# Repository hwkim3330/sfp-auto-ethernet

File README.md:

# sfp-auto-ethernet

SFP 모듈 세 가지. 호스트와는 SerDes로 붙고, 바깥쪽은 차량 이더넷이나 RJ45로 나간다.

- **폼팩터와 핀:** SFP(INF-8074i, SFF-8419)를 따른다. 전원·제어 핀과 EEPROM(SFF-8472)도 같다.
- **호스트 쪽 조건:**
  - T1과 T1S는 SGMII 1.25 Gbaud라서, 호스트 포트가 SGMII를 해야 한다. 1000BASE-X 전용 포트나 광모듈만 가정한 NIC에서는 안 된다.
  - RJ45는 2500BASE-X 3.125 Gbaud라서 "2.5G SFP"다. 1G 전용 SFP 슬롯에서는 안 되고, 2500BASE-X를 지원하는 포트(대개 SFP+ 케이지)가 필요하다.
- **표준이 아닌 부분:** 차량 이더넷(BASE-T1, T1S)을 SFP에 넣는 표준은 없다. SFF-8024에도 100/1000BASE-T1, 10BASE-T1S 코드가 없다. 그래서 EEPROM은 호스트에 1000BASE-T(RJ45는 2.5GBASE-T) 계열로 보이게 하고, 실제 매체는 벤더 영역에 적는다. 이것은 호환을 위한 우회이고, "표준 차량용 SFP"가 아니다. Intrepid나 Technica의 BASE-T1 SFP도 각사 자체 방식이다.
- **첫 검증 범위:** 정확히 아는 호스트 하나(D10 또는 LAN9692 EVB)로 한정한다. 범용 호환은 1차 목표가 아니다.

> **SFP 엣지 (2026-10-06 발견, 2026-10-08 세 보드 모두 수정):** 엣지 커넥터가 좌우 반전으로 그려져 있었다(SFF-8419 그림 7-2와 반대). 반전이 남아 있으면 VccT가 GND와 닿는다. T1, RJ45, T1S 모두 다시 배치·배선했고, 핑거 20개의 위치와 넷을 생성기와 독립된 기준으로 다시 확인했다([docs/COMPLIANCE.md](docs/COMPLIANCE.md) 3절).

| 변형 | 바깥쪽 | PHY | 호스트 쪽 | 커넥터 | 상태 |
|---|---|---|---|---|---|
| [`t1`](hw/t1/) | **100/1000BASE-T1** | TI DP83TG720S (1000) / DP83TC812S (100): 핀 호환이라 PCB 하나로 둘 다 | SGMII 1.25 Gbaud | H-MTD (Rosenberger E6S20A) | **엣지 수정 후 재배선(2026-10-07): DRC 0 / 미연결 0, ERC 0, KiCad 9 PASS, 주문 파일 있음.** MDI 종단은 TI OA 구성(1 kΩ 0.75 W 2010). 시제품 2~3장 후보. 실물·실측은 아직 없음 |
| [`rj45`](hw/rj45/) | 100M / 1G / **2.5GBASE-T** | Realtek RTL8221B-VB | 2500BASE-X 3.125 Gbaud 또는 SGMII | RJ45 (Kinghelm KH-RJ45-58, 차폐) | **엣지 수정 후 재배선(2026-10-07):** PHY를 윗면으로 옮겼다. DRC 0 / 미연결 0, ERC 0, KiCad 9 PASS, 패널 오류 0. SerDes와 MDI 모두 비아 없이 곧게 간다. 실물·실측은 아직 없음 |
| [`t1s`](hw/t1s/) | 10BASE-T1S | FPGA (Gowin GW5AT-15, SGMII PCS 브리지) + Microchip LAN8670 | SGMII 10 Mb/s | 2핀 (JST PH) | **엣지 수정 후 재배선(2026-10-08): DRC 0 / 미연결 0, ERC 0, KiCad 9 PASS, 패널 오류 0.** 두 SGMII 레인 모두 극성 그대로(게이트웨어 반전 없음). **주문 금지:** Gowin 트랜시버 IP 생성, 합성, P&R, 타이밍, 비트스트림이 끝나기 전에는 PCB를 주문하지 않는다 |

## 구조

```
 host SFP cage ── SerDes (AC 결합, 모듈 안) ──┐
                                              ▼
 I²C 0x50/0x51/0x56 ── STM32G031 ── MDIO ──► PHY ── (자기소자 / CMC) ── 커넥터
 TX_DISABLE · RX_LOS ──┘                      ▲
 3.3 V ── 페라이트 ── 부하 스위치(소프트 스타트) ── 벅 1.0 / 0.95 V ─┘
```

- **MCU 하나가 세 가지 일을 한다.** 호스트에게는 EEPROM(A0h/A2h)과 PHY 브리지(I²C 0x56)로 보이고, 링크 제어도 맡는다. 리눅스 `sfp` 드라이버가 기대하는 방식을 그대로 따랐다([docs/LINUX.md](docs/LINUX.md)).
- **데이터시트가 공개된 부품만 쓴다.** NDA가 필요한 PHY로는 설계도 유지보수도 못 한다. 88Q2112를 고르지 않은 이유다([docs/PARTS.md](docs/PARTS.md)). 예외는 하나, RJ45의 RTL8221B다: 누구나 내려받을 수 있지만 "CONFIDENTIAL" 도장이 찍힌 데이터시트이고, 2.5G를 하는 공개 데이터시트 PHY가 없어서 골랐다(같은 문서에 이유).
- **T1S에는 SGMII PHY가 없다.** 그래서 작은 FPGA가 SGMII 10 Mb/s를 받아 MII로 바꾸고, 반이중 버퍼도 맡는다.

## 설계 원칙 (설계 검토 뒤)

- **적층** (모두 1.0 mm, 같은 3313 프리프레그라 쌍 치수가 같다):
  - **T1은 4층 F / GND / GND / B** (JLC04101H-3313). 두 안쪽 층 모두 GND다. In2에는 저속 신호도 지나가지만, 아래층(B)을 달리는 고속 쌍 밑에는 금지 구역을 두어 판을 온전히 남긴다.
  - **RJ45·T1S는 6층 F / GND / 신호 / +3V3 / GND / B** (JLC06101H-3313). T1S는 In4 GND 안에 0.95 V 코어 섬을 둔다.
  - 그래서 모든 고속 쌍이 어느 층에 있든 GND를 기준으로 삼는다.
- **고속 쌍은 손으로 결합해서 깐다.** 선폭 0.114, 간격 0.152로 약 100 Ω 차동이다.
  - 쌍 안의 두 선은 같은 층, 같은 비아 수로 간다.
  - 층을 바꾸는 곳 옆에는 GND 비아를 둔다.
  - 라우터(Freerouting)는 나머지 저속 신호만 맡는다.
- **3.3 V 인러시**: 핫플러그하면 호스트 필터가 전압을 수십 µs 만에 올린다. 그래서 모듈 입력에 **TPS22918 부하 스위치**(약 3.6 ms 상승)를 넣었다. MSA의 "정상 상태 대비 +30 mA 이내"를 설계로 맞췄다. **실물 측정은 아직이다.**
- **보드 몸통은 폭 11.8 mm**다. 탭은 9.2 mm, 케이지 안 높이 한도는 위 4.65 mm, 아래 1.65 mm다. 치수 출처는 [docs/SFP_MSA.md](docs/SFP_MSA.md)에 있다.

## 검증 (하드웨어 없이 할 수 있는 것)

| 무엇 | 도구 | 어디서 |
|---|---|---|
| DRC, 회로도-PCB 일치(parity), ERC | KiCad 9 (공식 Docker 이미지). 검토자가 여는 그대로 | `sh hw/check_kicad9.sh t1`, `… rj45`, `… t1s` |
| 펌웨어 빌드: 4가지 변형, 경고 0 | arm-none-eabi-gcc | `fw/`, CI |
| T1S 게이트웨어 | Icarus Verilog 테스트벤치 3개 | `hw/t1s/gw/`, CI |
| 규격 대조: 임피던스(자체 2D 전계 해석기), 쌍 스큐 대 심볼 시간, 엣지 핑거 치수, 케이지 높이, 클럭 ppm, 제어 핀 타이밍, 커넥터 | `tools/zsolve.py`, `tools/compliance.py` | [docs/COMPLIANCE.md](docs/COMPLIANCE.md) |
| 레퍼런스 대조: TI·Realtek·Microchip·Gowin 데이터시트·앱노트·EVM, 리눅스 드라이버, 상용 모듈 | 문서별 값 대조 | [docs/REFERENCES.md](docs/REFERENCES.md) |

- GitHub Actions([.github/workflows/check.yml](.github/workflows/check.yml))가 push할 때마다 위 셋을 다시 돌린다.
- KiCad 9 검사에서 허용하는 경고는 "라이브러리 사본이 다르다" 두 종류뿐이다. KiCad 9 라이브러리가 KiCad 7 원본보다 새 판이라서 생긴다.

## 아직 실물로만 확인할 수 있는 것

- **펌웨어는 보드에서 0회 돌았다.** 보드가 오면 확인할 것:
  - MDC/MDIO 타이밍, 시작 시퀀스, TX_DISABLE/RX_LOS 동작;
  - SGMII 극성(세 보드 모두 반전 없이 P–P로 깔았다).
- **인러시 전류와 3.3 V 상승 시간.** 오실로스코프로 잰다.
- **H-MTD 풋프린트.** `hw/t1/fab/t1-1to1.pdf`를 100 %로 인쇄하고 실물 커넥터를 대 본다.
- **골드 핑거.** JLC는 경질 금(hard gold)을 하지 않고 ENIG만 한다. MSA 규격(경질 금 ≥ 0.38 µm)은 아니다. 시험용 삽입 수십 회는 쓸 만하다. 반복 삽입이 많다면 경질 금을 하는 업체(예: PCBWay)에 맡긴다.
- **RJ45 코 폭 17 mm.** 잭 자체가 15.7 mm다. D10에서 옆 포트와 부딪히는지 실측해야 한다.

## Kontron D10에 꽂는다면

[docs/D10.md](docs/D10.md): D10의 SFP 포트는 **최대 2.5G**다.
- T1: `make HOST=d10` 펌웨어로 굽는다(1000BASE-X로 보이고 SGMII AN은 끈다).
- RJ45: 호스트 쪽을 2500BASE-X로 고정한다. D10이 2.5G-T 모듈을 속도 2500 고정에서만 붙이기 때문이다.

## 다음

1. T1S 게이트웨어: Gowin 트랜시버 IP 생성, 합성, 타이밍
2. 하우징: 래치와 베일

## 참고

- 비슷한 상용 제품이 있다. 그러니 이 크기 안에 들어간다.
  - [Intrepid 88Q2112 SFP](https://intrepidcs.com/products/automotive-ethernet-tools/88q2112-1000base-t1-sfp/): 76.5 × 13.5 × 20.5 mm, H-MTD
  - [Technica TE-1441](https://technica-engineering.de/en-gb/hardware-products/sfp-sfp-modules): I²C → MDIO 게이트웨이, DIP 스위치
- 10G RJ45 SFP+는 만들지 않는다. 10GBASE-T PHY는 2.5–5 W를 쓰고 NDA 부품이다. 게다가 D10 포트는 2.5G까지다.

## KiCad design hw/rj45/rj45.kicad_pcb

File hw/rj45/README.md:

# RJ45 SFP: 100M / 1G / 2.5GBASE-T

A copper SFP built around the Realtek RTL8221B. It runs 2500BASE-X (3.125 Gbaud) or SGMII to the host, and 100M / 1G / 2.5GBASE-T on the jack.

Schematic, 6-layer PCB (routed), fab outputs and a JLC panel are all in place.
**Order files are in [`jlc/`](jlc/), and the order sheet is [ORDER.md](ORDER.md).** Nothing has been built.

| Top | Bottom |
|---|---|
|  |  |

## Status

| | Result | How it was checked |
|---|---|---|
| Schematic | **ERC 0 errors, 0 warnings** ([erc.rpt](erc.rpt)) | eeschema's own ERC (`run_erc.sh`) |
| Placement | 70 footprints, no overlaps; housing height limits met | `make_rj45.py` |
| Routing | **DRC 0 violations, 0 unconnected** ([drc.rpt](drc.rpt)) | hand-laid pairs and buses, Freerouting 1.9.0 for the rest, then KiCad DRC |
| KiCad 9 | **DRC 0 errors, 0 unconnected, schematic parity clean, ERC 0 errors** ([kicad9-drc.rpt](kicad9-drc.rpt), [kicad9-erc.rpt](kicad9-erc.rpt)) | `sh ../check_kicad9.sh rj45`: the official KiCad 9 image. Only warnings are "differs from the library copy" |
| Fab | Gerbers + drill ([fab/rj45-gerbers.zip](fab/rj45-gerbers.zip)), [BOM](fab/rj45-bom.csv), [CPL](fab/rj45-cpl.csv), [1:1 print](fab/rj45-1to1.pdf) | `export_rj45.py` |
| Panel | 5 boards, 71.5 × 107.1 mm, **DRC 0 errors, 0 unconnected** with the board's rules ([jlc/panel-drc.rpt](jlc/panel-drc.rpt)) | `panel_rj45.py` (KiKit) |
| Pair lengths | [lengths.txt](lengths.txt) | `make_rj45.py` |

## Parts (all in JLC stock, 2026-09-30)

| | Part | LCSC | Stock |
|---|---|---|---|
| PHY | Realtek RTL8221B-VB-CG | C5155988 | 4564 |
| Magnetics | LINK-PP LP72450ANL (2.5G, 4 channels, 15.2 × 7.1 × 4.3 mm) | C53281905 | 800 |
| Jack | Kinghelm KH-RJ45-58-8P8C, shielded, no magnetics | C2683360 | 2717 |
| Clock | MST8011AI 25 MHz oscillator (≤ 2 ps RMS jitter, as the PHY asks) | C51026225 | 898 |
| Core 0.946 V | TPS62822 buck, 57.6k / 100k | C473385 | 2288 |
| Inrush | TPS22918 load switch, 2.2 nF CT (≈ 3.6 ms) | C131941 | 12874 |
| MCU | STM32G031F6P6 | C529333 | 1454 |

Parts come to about $11 a board.

## Board

- The body is 11.8 mm wide up to the cage front. From there a 17 mm nose carries the jack, which sits entirely outside the cage. The board is 64.4 mm long.
- **Six layers, JLC06101H-3313.** The same 3313 prepreg (0.0994 mm, Dk 4.1) sits under F and B as on the 4-layer stack, so the pairs keep 0.114 mm lines with a 0.152 mm gap (≈ 100 Ω differential).

  | Layer | Use |
  |---|---|
  | F | U1 and its decaps, both SerDes pairs, the MDI pairs under the magnetics, the line side |
  | In1 | GND |
  | In2 | the slow lines, hand-laid end to end (fingers and U1 to the MCU) |
  | In3 | +3V3 plane |
  | In4 | GND |
  | B | the buck, the power-entry caps, the oscillator and analog beads, line pair 2, the MCU |

- **Why six:** on four layers every signal routed, but the PHY's power pins did not all reach their rails. They sit 0.4 mm apart with their decaps right next to them. Here every +3V3 pad has its own via into the In3 plane.
- **Pairs, all laid by hand and coupled** (`make_rj45.py`):
  - SerDes to the host. U1 sits on top, turned 90°. Its pins 37–41 read HSON, HSOP, HSIP, HSIN top to bottom, the order of the SFP edge's RD−, RD+, TD+, TD− (SFF-8419 Figure 7-2). Both pairs run straight, P to P, on top, with no via.
    (Until 2026-10 the edge was drawn mirrored and U1 sat underneath for the same reason; `make_rj45.py` turns that group over.)
  - The four MDI pairs run on top under the magnetics' body and straight into its chip-side pads, in port order: port 0 on channel 1 (jack 1/2) … port 3 on channel 4. CFG_OPT1 is pulled down, so there is no MDI swap.
- **PHY address straps:** the RTL8221B has no internal pulls on its CONFIG pins (datasheet 7.18: an external pull-high or pull-low is required). LED0/1/2 carry PHYAD[2:0]: R19-R21, 4.7 kΩ to ground, give 000, which the PHY treats as address 1 (Table 16 note 2), the address the firmware uses. Three 0201s right above pins 33-35 on top; C16 moved underneath its via and C17 0.3 mm west to make room.
  - Line pairs 0, 1 and 3 run on top in lanes 0.8 mm apart.
  - Line pair 2 (jack pins 4/5) drops to the bottom under its pads. Pair 3/6 straddles 4/5 on the jack, so one of those two pairs has to leave the top side.
- **The MCU sits under the jack.** It is the only place with room. Its ten slow lines run on In2, laid by hand from end to end:
  - they leave the fingers and U1 through vias;
  - they run in the board's lane order to the jack's pin field;
  - they cross the field in three lanes of three, plus MDIO underneath.
  - The MCU's GPIOs are assigned to match the lane order, not the T1 board's: PA0 MDIO, PA1 MDC, PA4 TX_FAULT, PA5 TX_DISABLE, PA6 RX_LOS (`fw/main.c`, `VARIANT_RJ45`).
- **In2 keepouts:** the MDI and line pairs are 2.5GBASE-T at 200 MBd PAM16, so In2 lines may cross under them. On six layers the bottom pairs reference In4 GND anyway.

## Regenerating

```bash
python3 make_rj45.py            # symbols, footprints, schematic, placed PCB
python3 make_rj45.py --route    # planes, dogbones, Freerouting, pours, repairs, DRC -> drc.rpt
sh run_erc.sh                   # eeschema ERC -> erc.rpt
sh ../check_kicad9.sh rj45      # the same board in KiCad 9
python3 export_rj45.py          # gerbers (6 copper layers), BOM, CPL, previews, 1:1 PDF -> fab/
python3 panel_rj45.py           # 5-board panel + JLC files -> jlc/
```

## Not verified

- Nothing has been built.
- **Firmware for this variant** (`fw/`, `VARIANT=rj45`) builds, but has never run. Check:
  - the MDIO access to the RTL8221B;
  - 2500BASE-X / SGMII selection;
  - LED / link reporting.
- **Jack land:** it is drawn from Kinghelm's drawing by hand. Print `fab/rj45-1to1.pdf` at 100 % and set a real jack on it.
- **Fit next to other modules:** the jack is 15.7 mm wide, against 13.7 mm for a copper SFP's housing. It may touch its neighbour in a ganged cage (for example on the D10). Measure it.
- **Inrush and the 0.95 V rise time:** measure them.

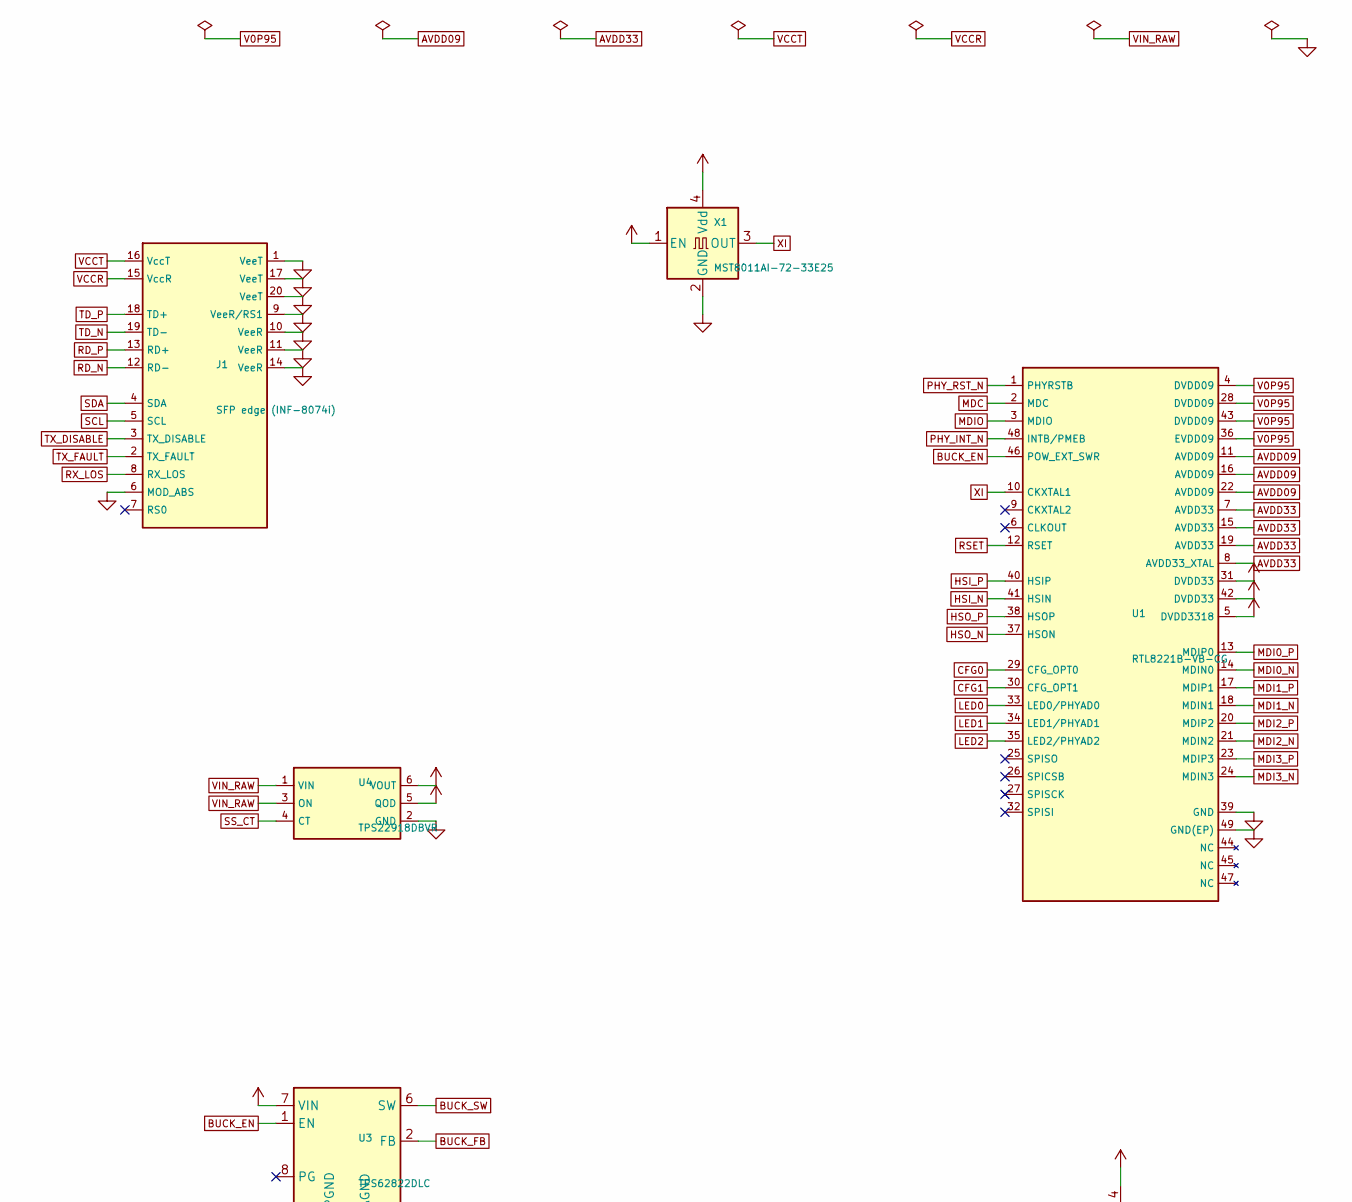
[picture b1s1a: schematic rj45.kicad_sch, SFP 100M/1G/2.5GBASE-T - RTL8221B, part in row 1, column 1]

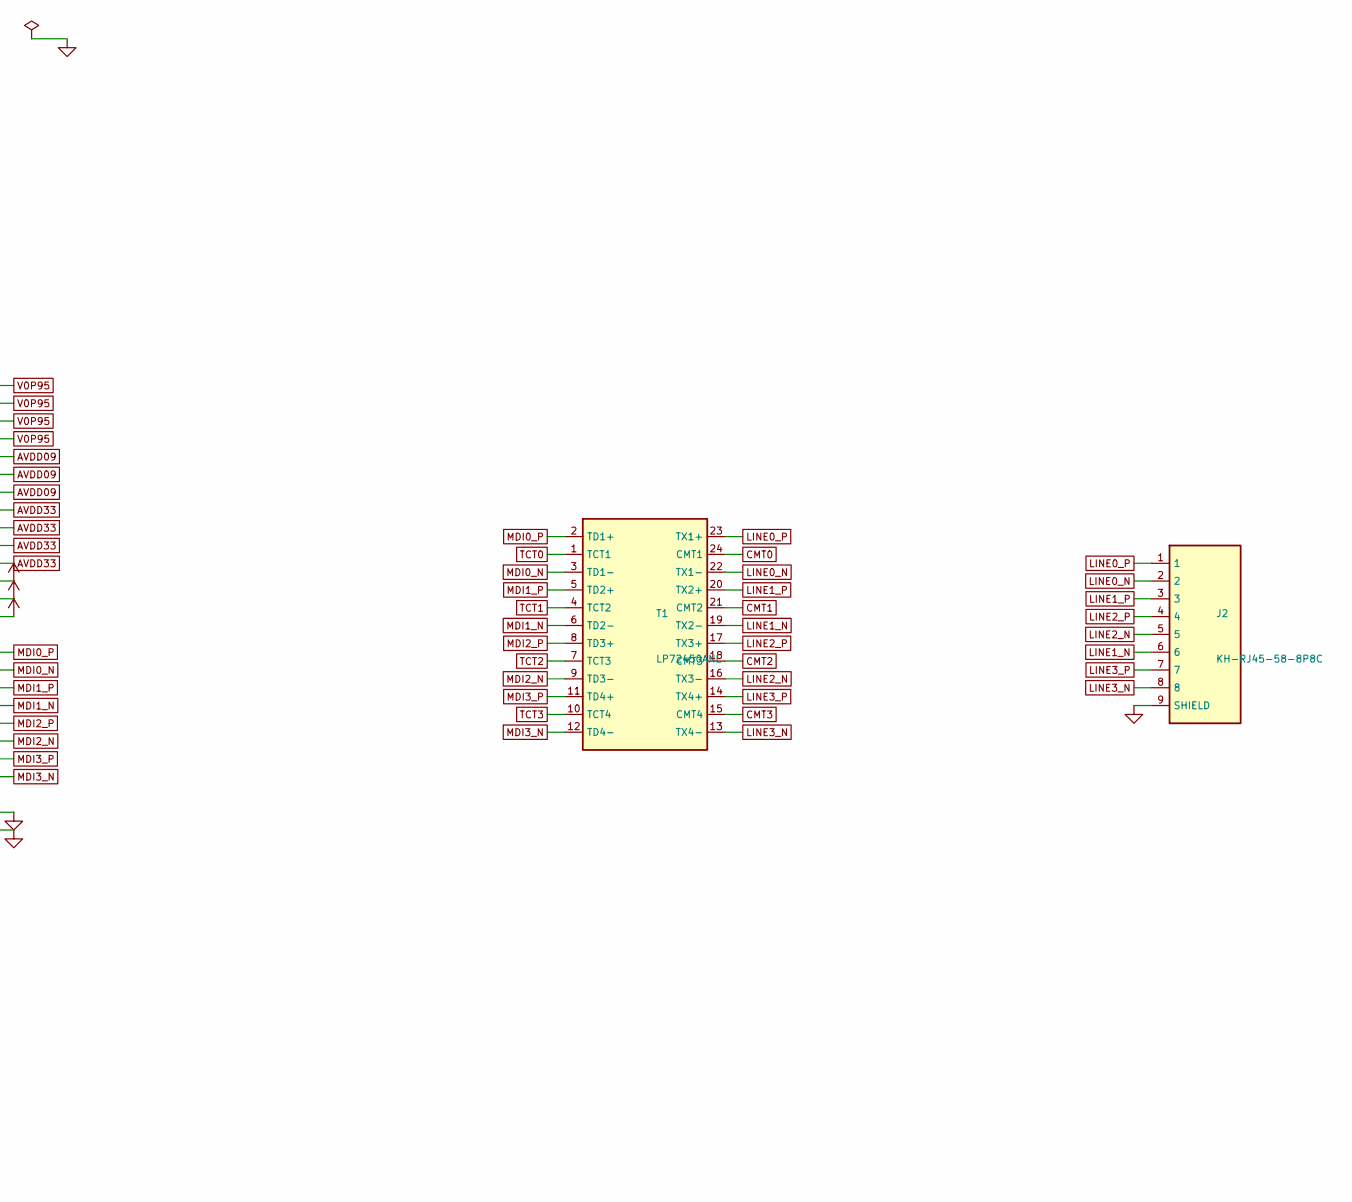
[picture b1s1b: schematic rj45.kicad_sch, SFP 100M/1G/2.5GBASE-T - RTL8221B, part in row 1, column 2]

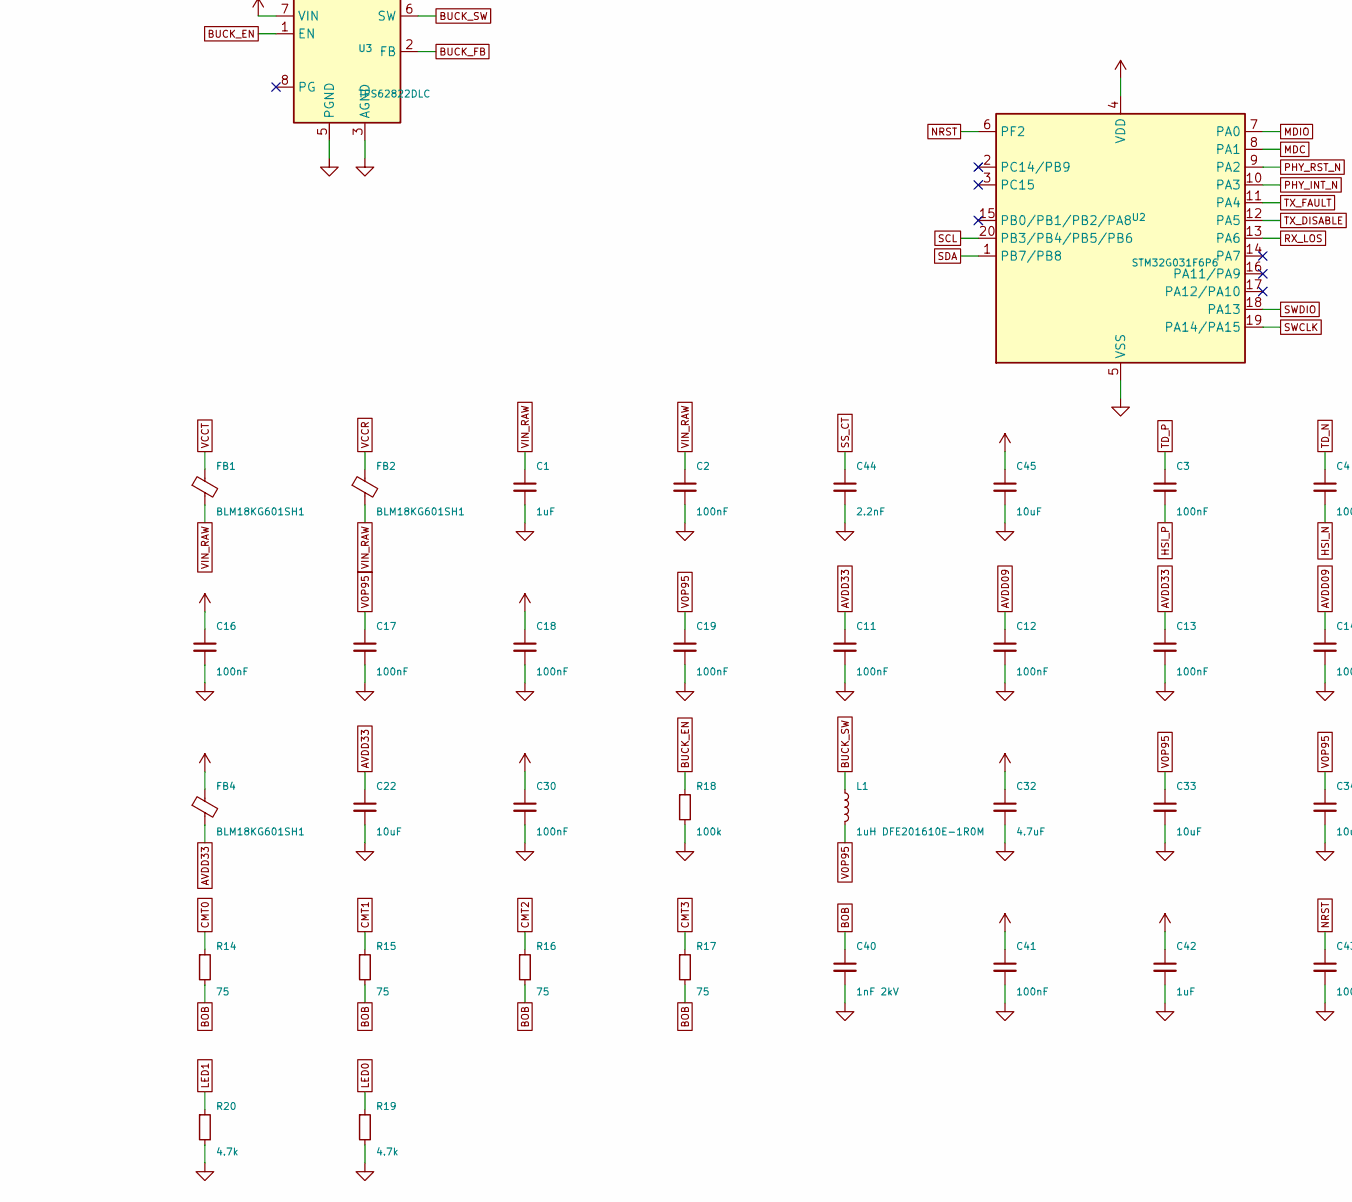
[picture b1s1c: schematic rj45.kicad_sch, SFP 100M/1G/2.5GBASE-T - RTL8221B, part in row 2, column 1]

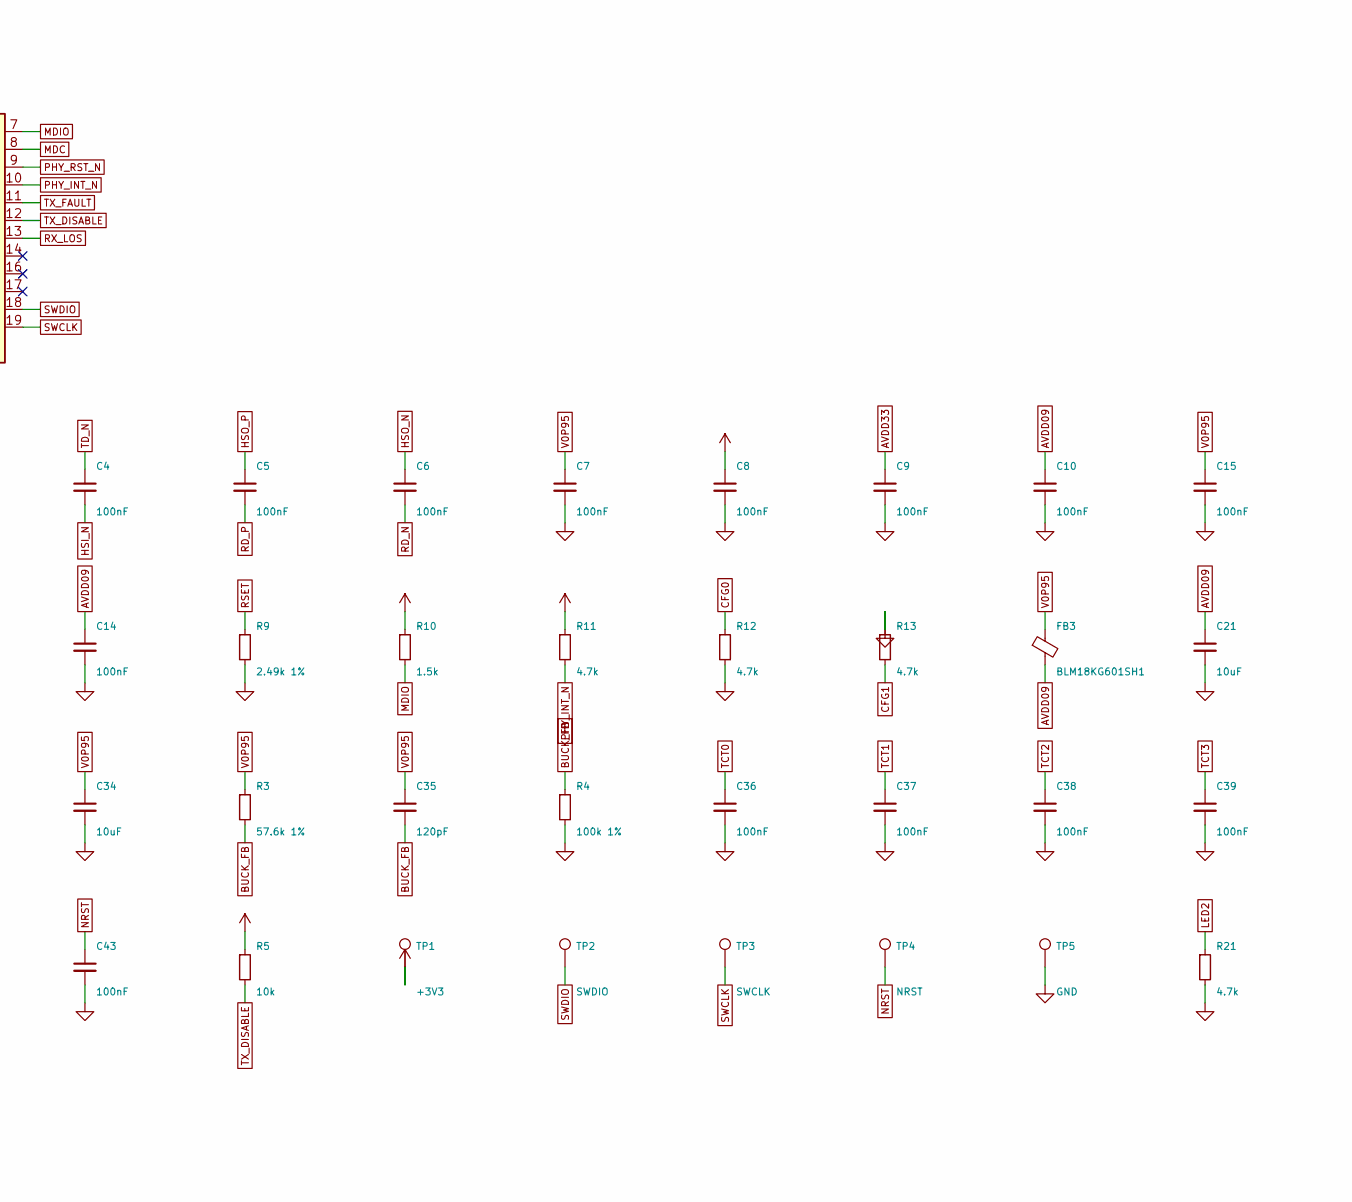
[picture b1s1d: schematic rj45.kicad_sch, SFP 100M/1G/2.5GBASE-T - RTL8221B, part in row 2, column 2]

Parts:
C1, C42: 1uF; C_0402_1005Metric; LCSC C52923
C2, C5, C6, C36, C37, C38, C39, C41, C43: 100nF; C_0402_1005Metric; LCSC C1525
C3, C4, C7, C8, C9, C10, C11, C12, C13, C14, C15, C16, C17, C18, C19, C30: 100nF; C_0201_0603Metric; LCSC C76928
C21, C22, C33, C34, C45: 10uF; C_0603_1608Metric; LCSC C19702
C32: 4.7uF; C_0402_1005Metric; LCSC C23733
C35: 120pF; C_0201_0603Metric; LCSC C161406
C40: 1nF 2kV; C_1206_3216Metric; MPN 1206B102K202NT; LCSC C9196
C44: 2.2nF; C_0402_1005Metric; LCSC C106861
FB1, FB2, FB3, FB4: BLM18KG601SH1; L_0603_1608Metric; MPN BLM18KG601SH1; LCSC C710379
J1: SFP edge (INF-8074i); SFP_Module_Edge
J2: KH-RJ45-58-8P8C; RJ45_Kinghelm_KH-RJ45-58; MPN KH-RJ45-58-8P8C; LCSC C2683360
L1: 1uH DFE201610E-1R0M; L_Murata_DFE201610P; MPN DFE201610E-1R0M; LCSC C161082
R3: 57.6k 1%; R_0201_0603Metric; LCSC C423476
R4: 100k 1%; R_0201_0603Metric; LCSC C106224
R5: 10k; R_0402_1005Metric; LCSC C25744
R9: 2.49k 1%; R_0201_0603Metric; LCSC C473476
R10: 1.5k; R_0201_0603Metric; LCSC C270361
R11, R12, R13, R19, R20, R21: 4.7k; R_0201_0603Metric; LCSC C142008
R14, R15, R16, R17: 75; R_0402_1005Metric; LCSC C25133
R18: 100k; R_0201_0603Metric; LCSC C106224
T1: LP72450ANL; LINKPP_LP72450ANL; MPN LP72450ANL; LCSC C53281905
TP1: +3V3; TestPoint_Pad_D1.0mm
TP2: SWDIO; TestPoint_Pad_D1.0mm
TP3: SWCLK; TestPoint_Pad_D1.0mm
TP4: NRST; TestPoint_Pad_D1.0mm
TP5: GND; TestPoint_Pad_D1.0mm
U1: RTL8221B-VB-CG; QFN-48-1EP_6x6mm_P0.4mm_EP4.3x4.3mm; MPN RTL8221B-VB-CG; LCSC C5155988
U2: STM32G031F6P6; TSSOP-20_4.4x6.5mm_P0.65mm; MPN STM32G031F6P6; LCSC C529333
U3: TPS62822DLC; Texas_VSON-HR-8_1.5x2mm_P0.5mm; MPN TPS62822DLCR; LCSC C473385
U4: TPS22918DBVR; SOT-23-6; MPN TPS22918DBVR; LCSC C131941
X1: MST8011AI-72-33E25; Oscillator_SMD_MST_2016-4Pin; MPN MST8011AI-72-33E25.000000; LCSC C51026225

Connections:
+3V3: C8.1, C16.1, C18.1, C30.1, C32.1, C41.1, C42.1, C45.1, FB4.1, R5.1, R10.1, R11.1, TP1.1, U1.5 (DVDD3318), U1.31 (DVDD33), U1.42 (DVDD33), U2.4 (VDD), U3.7 (VIN), U4.5 (QOD), U4.6 (VOUT), X1.1 (EN), X1.4 (Vdd)
AVDD09: C10.1, C12.1, C14.1, C21.1, FB3.2, U1.11 (AVDD09), U1.16 (AVDD09), U1.22 (AVDD09)
AVDD33: C9.1, C11.1, C13.1, C22.1, FB4.2, U1.7 (AVDD33), U1.8 (AVDD33_XTAL), U1.15 (AVDD33), U1.19 (AVDD33)
BOB: C40.1, R14.2, R15.2, R16.2, R17.2
BUCK_EN: R18.1, U1.46 (POW_EXT_SWR), U3.1 (EN)
BUCK_FB: C35.2, R3.2, R4.1, U3.2 (FB)
BUCK_SW: L1.1, U3.6 (SW)
CFG0: R12.1, U1.29 (CFG_OPT0)
CFG1: R13.2, U1.30 (CFG_OPT1)
CMT0: R14.1, T1.24 (CMT1)
CMT1: R15.1, T1.21 (CMT2)
CMT2: R16.1, T1.18 (CMT3)
CMT3: R17.1, T1.15 (CMT4)
GND: C1.2, C2.2, C7.2, C8.2, C9.2, C10.2, C11.2, C12.2, C13.2, C14.2, C15.2, C16.2, C17.2, C18.2, C19.2, C21.2, C22.2, C30.2, C32.2, C33.2, C34.2, C36.2, C37.2, C38.2, C39.2, C40.2, C41.2, C42.2, C43.2, C44.2, C45.2, J1.1 (VeeT), J1.6 (MOD_ABS), J1.9 (VeeR/RS1), J1.10 (VeeR), J1.11 (VeeR), J1.14 (VeeR), J1.17 (VeeT), J1.20 (VeeT), J2.9 (SHIELD), R4.2, R9.2, R12.2, R13.1, R18.2, R19.2, R20.2, R21.2, TP5.1, U1.39 (GND), U1.49 (GND(EP)), U2.5 (VSS), U3.3 (AGND), U3.5 (PGND), U4.2 (GND), X1.2 (GND)
HSI_N: C4.2, U1.41 (HSIN)
HSI_P: C3.2, U1.40 (HSIP)
HSO_N: C6.1, U1.37 (HSON)
HSO_P: C5.1, U1.38 (HSOP)
LED0: R19.1, U1.33 (LED0/PHYAD0)
LED1: R20.1, U1.34 (LED1/PHYAD1)
LED2: R21.1, U1.35 (LED2/PHYAD2)
LINE0_N: J2.2, T1.22 (TX1-)
LINE0_P: J2.1, T1.23 (TX1+)
LINE1_N: J2.6, T1.19 (TX2-)
LINE1_P: J2.3, T1.20 (TX2+)
LINE2_N: J2.5, T1.16 (TX3-)
LINE2_P: J2.4, T1.17 (TX3+)
LINE3_N: J2.8, T1.13 (TX4-)
LINE3_P: J2.7, T1.14 (TX4+)
MDC: U1.2 (MDC), U2.8 (PA1)
MDI0_N: T1.3 (TD1-), U1.14 (MDIN0)
MDI0_P: T1.2 (TD1+), U1.13 (MDIP0)
MDI1_N: T1.6 (TD2-), U1.18 (MDIN1)
MDI1_P: T1.5 (TD2+), U1.17 (MDIP1)
MDI2_N: T1.9 (TD3-), U1.21 (MDIN2)
MDI2_P: T1.8 (TD3+), U1.20 (MDIP2)
MDI3_N: T1.12 (TD4-), U1.24 (MDIN3)
MDI3_P: T1.11 (TD4+), U1.23 (MDIP3)
MDIO: R10.2, U1.3 (MDIO), U2.7 (PA0)
NRST: C43.1, TP4.1, U2.6 (PF2)
PHY_INT_N: R11.2, U1.48 (INTB/PMEB), U2.10 (PA3)
PHY_RST_N: U1.1 (PHYRSTB), U2.9 (PA2)
RD_N: C6.2, J1.12 (RD-)
RD_P: C5.2, J1.13 (RD+)
RSET: R9.1, U1.12 (RSET)
RX_LOS: J1.8 (RX_LOS), U2.13 (PA6)
SCL: J1.5 (SCL), U2.20 (PB3/PB4/PB5/PB6)
SDA: J1.4 (SDA), U2.1 (PB7/PB8)
SS_CT: C44.1, U4.4 (CT)
SWCLK: TP3.1, U2.19 (PA14/PA15)
SWDIO: TP2.1, U2.18 (PA13)
TCT0: C36.1, T1.1 (TCT1)
TCT1: C37.1, T1.4 (TCT2)
TCT2: C38.1, T1.7 (TCT3)
TCT3: C39.1, T1.10 (TCT4)
TD_N: C4.1, J1.19 (TD-)
TD_P: C3.1, J1.18 (TD+)
TX_DISABLE: J1.3 (TX_DISABLE), R5.2, U2.12 (PA5)
TX_FAULT: J1.2 (TX_FAULT), U2.11 (PA4)
V0P95: C7.1, C15.1, C17.1, C19.1, C33.1, C34.1, C35.1, FB3.1, L1.2, R3.1, U1.4 (DVDD09), U1.28 (DVDD09), U1.36 (EVDD09), U1.43 (DVDD09)
VCCR: FB2.1, J1.15 (VccR)
VCCT: FB1.1, J1.16 (VccT)
VIN_RAW: C1.1, C2.1, FB1.2, FB2.2, U4.1 (VIN), U4.3 (ON)
XI: U1.10 (CKXTAL1), X1.3 (OUT)

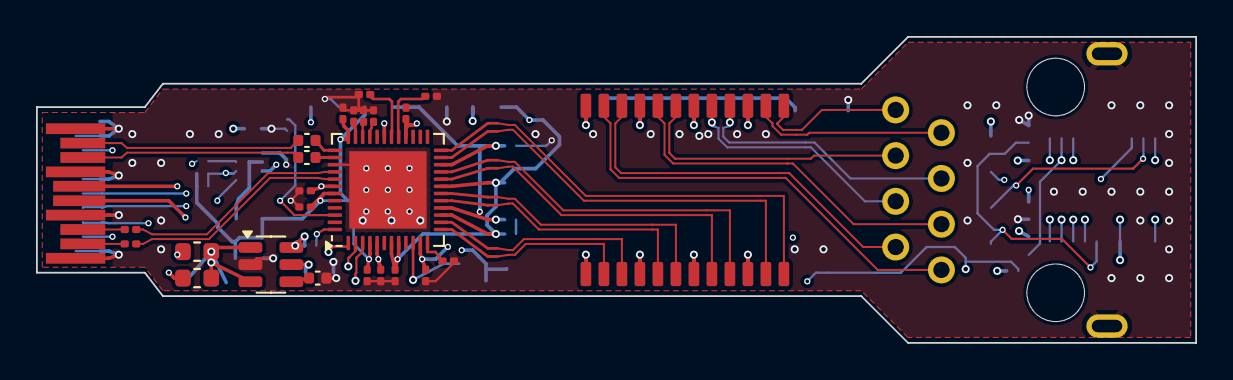
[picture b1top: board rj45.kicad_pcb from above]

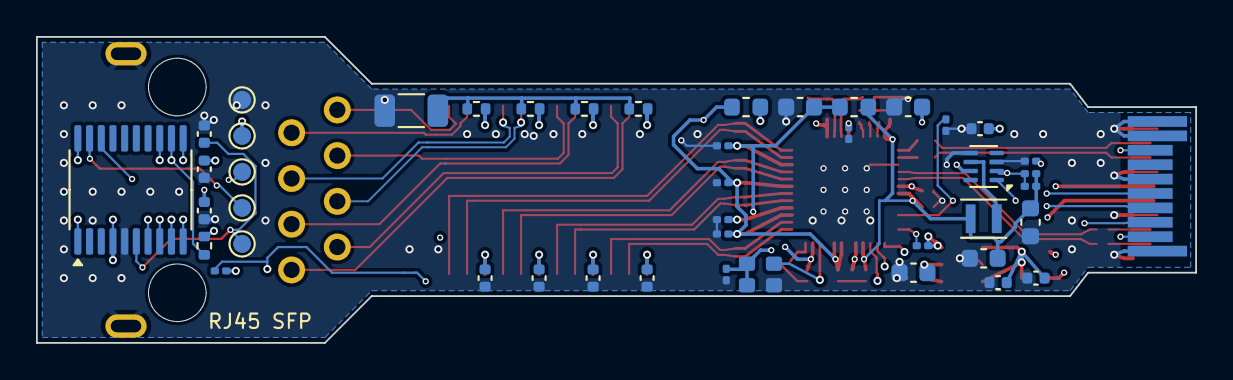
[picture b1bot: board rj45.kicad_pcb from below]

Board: 6 copper layers, 64.4 x 17.0 mm, 70 parts (44 on the bottom side), 64 nets.

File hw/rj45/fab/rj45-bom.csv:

Comment,Designator,Footprint,MPN,Qty,Fitted
1uF,"C1,C42",C_0402_1005Metric,,2,yes
100nF,"C2,C5,C6,C36,C37,C38,C39,C41,C43",C_0402_1005Metric,,9,yes
100nF,"C3,C4,C7,C8,C9,C10,C15,C16,C17,C18,C19,C11,C12,C13,C14,C30",C_0201_0603Metric,,16,yes
4.7uF,C32,C_0402_1005Metric,,1,yes
120pF,C35,C_0201_0603Metric,,1,yes
1nF 2kV,C40,C_1206_3216Metric,1206B102K202NT,1,yes
2.2nF,C44,C_0402_1005Metric,,1,yes
10uF,"C45,C21,C22,C33,C34",C_0603_1608Metric,,5,yes
BLM18KG601SH1,"FB1,FB2,FB3,FB4",L_0603_1608Metric,BLM18KG601SH1,4,yes
KH-RJ45-58-8P8C,J2,RJ45_Kinghelm_KH-RJ45-58,KH-RJ45-58-8P8C,1,yes
1uH DFE201610E-1R0M,L1,L_Murata_DFE201610P,DFE201610E-1R0M,1,yes
1.5k,R10,R_0201_0603Metric,,1,yes
4.7k,"R11,R12,R13,R21,R20,R19",R_0201_0603Metric,,6,yes
75,"R14,R15,R16,R17",R_0402_1005Metric,,4,yes
100k,R18,R_0201_0603Metric,,1,yes
57.6k 1%,R3,R_0201_0603Metric,,1,yes
100k 1%,R4,R_0201_0603Metric,,1,yes
10k,R5,R_0402_1005Metric,,1,yes
2.49k 1%,R9,R_0201_0603Metric,,1,yes
LP72450ANL,T1,LINKPP_LP72450ANL,LP72450ANL,1,yes
RTL8221B-VB-CG,U1,QFN-48-1EP_6x6mm_P0.4mm_EP4.3x4.3mm,RTL8221B-VB-CG,1,yes
STM32G031F6P6,U2,TSSOP-20_4.4x6.5mm_P0.65mm,STM32G031F6P6,1,yes
TPS62822DLC,U3,Texas_VSON-HR-8_1.5x2mm_P0.5mm,TPS62822DLCR,1,yes
TPS22918DBVR,U4,SOT-23-6,TPS22918DBVR,1,yes
MST8011AI-72-33E25,X1,Oscillator_SMD_MST_2016-4Pin,MST8011AI-72-33E25.000000,1,yes
